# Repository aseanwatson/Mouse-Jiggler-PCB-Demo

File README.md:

# Mouse-Jiggler-PCB-Demo
This is a PCB designed in KiCAD as a demo for Seattle Makers.

It's based on [Arduino based Mouse Jiggler](https://github.com/MAKERSUN99/MAUS) 
published on GitHub. MAKERSUN99 published the schematic and the PCB as
a PDF so the circut and basic layout is clear, but not the original KiCAD
files.

It is a good demo because it can be incrementally designed. At its core,
it is a USB A male connector and an ATTINY85. The ATTINY can do raw GPIO
manipulation to handle USB connectivity and so it can emulate a mouse.

But USB devices should have ESD protection and so you can add that as a
pair of zener diodes and a capacitor.

Similarly, the ATTINY is supposed to have a capacitor close to VCC to condition
power for it.

Once that is done, you still ought to have a way to program the ATTINY so, you
can add a 1x5 pin header to connect to VCC, GND, PB2, PB3,and PB4.

After that, it's nice to have a LED and an associated resistor to show
activity.

Finally, you can add a WS2812B/NeoPixel for more interesting light effects.

## Steps to build it in KiCAD
Components:

|Part Description|Manufacturer Part Number|LCSC Part Number|
|-|-|-:|
|100nF Capacitor|CL21B104KBCNNNC|[C1711](https://www.lcsc.com/datasheet/lcsc_datasheet_2304140030_Samsung-Electro-Mechanics-CL21B104KBCNNNC_C1711.pdf)|
|100uF Capacitor|CL31A107MQHNNNE|[C15008](https://www.lcsc.com/datasheet/lcsc_datasheet_2304140030_Samsung-Electro-Mechanics-CL31A107MQHNNNE_C15008.pdf)|
|Zener Diode|MM1Z5226B|[C118713](https://www.lcsc.com/datasheet/lcsc_datasheet_2304140030_ST-Semtech-MM1Z5226B_C118713.pdf)|
|LED|XL-2012VRC|[C7371913](https://www.lcsc.com/datasheet/lcsc_datasheet_2402181500_XINGLIGHT-XL-2012VRC_C7371913.pdf)|
|1x5 male header|DS1021-1x5SF11-B|[C7430361](https://www.lcsc.com/datasheet/lcsc_datasheet_2312201431_CONNFLY-Elec-DS1021-1x5SF11-B_C7430361.pdf)|
|NeoPixel|WS2812B-B/T|[C2761795](https://www.lcsc.com/datasheet/lcsc_datasheet_2106062036_Worldsemi-WS2812B-B-T_C2761795.pdf)|
|68 Ohm Resistor|FRC0805J680 TS|[C2907341](https://www.lcsc.com/datasheet/lcsc_datasheet_2308241947_FOJAN-FRC0805J680-TS_C2907341.pdf)|
|1.5k Ohm Resistor|FRC0805J152 TS|[C2907290](https://www.lcsc.com/datasheet/lcsc_datasheet_2308241947_FOJAN-FRC0805J152-TS_C2907290.pdf)|
|220 Ohm Resistor|FRC0805J221 TS|[C2933537](https://www.lcsc.com/datasheet/lcsc_datasheet_2308241113_FOJAN-FRC0805J221-TS_C2933537.pdf)|
|10k Ohm Resistor|FRC0805J103TS|[C2930231](https://www.lcsc.com/datasheet/lcsc_datasheet_2308241947_FOJAN-FRC0805J103TS_C2930231.pdf)|
|ATTiny85 MPU|ATTINY85-20SU|[C89852](https://www.lcsc.com/datasheet/lcsc_datasheet_2011170235_Microchip-Tech-ATTINY85-20SU_C89852.pdf)|
|Male USB A Connector|KH-USB180-AM-4P|[C2828094](https://www.lcsc.com/datasheet/lcsc_datasheet_2105241835_Shenzhen-Kinghelm-Elec-KH-USB180-AM-4P_C2828094.pdf)|

KiCAD has the footprints and symbols for most of the above, but you need
to get the footprints from LCSC for three. To do that run this PowerShell:

``` powershell
cd $env:TEMP
python -m venv easyeda2kicad\.venv
. .\easyeda2kicad\.venv\Scripts\Activate.ps1
easyeda2kicad.exe --full --lcsc_id=C2761795
easyeda2kicad.exe --full --lcsc_id=C89852
easyeda2kicad.exe --full --lcsc_id=C2828094
```

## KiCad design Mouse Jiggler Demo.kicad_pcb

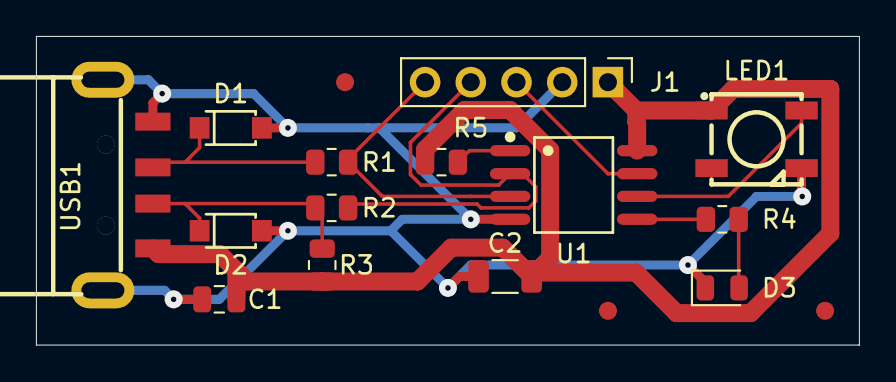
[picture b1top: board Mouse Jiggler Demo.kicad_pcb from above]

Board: 2 copper layers, 45.7 x 17.1 mm, 14 parts (0 on the bottom side), 11 nets.

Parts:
C1: 100n; C_0805_2012Metric
C2: 100u; C_1206_3216Metric
D1, D2: BZT52-C3V3_R1_00001; SOD-123_L2.7-W1.6-LS3.8-RD
D3: LED; LED_0805_2012Metric
J1: Conn_01x05_Pin; PinHeader_1x05_P2.54mm_Vertical
LED1: WS2812B-XF02/W; LED-SMD_4P-L5.0-W5.0-TL
R1, R2: 68; R_0805_2012Metric
R3: 1k5; R_0805_2012Metric
R4: 220; R_0805_2012Metric
R5: 10k; R_0805_2012Metric
U1: ATTINY85-20SUR; SOIC-8_L5.3-W5.3-P1.27-LS8.0-BL
USB1: U-G-04WS-W-04; USB-TH_U-G-04WS-W-04

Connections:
+5V: C1.1, C2.2, J1.1, LED1.1 (VDD), R3.1, R5.1, U1.8 (VCC), USB1.1 (VCC)
D+ PB4: J1.5, R1.2, U1.3 (PB4)
D- PB3: J1.4, R2.2, U1.2 (PB3)
GND: C1.2, C2.1, D1.2 (A), D2.2 (A), D3.1 (K), J1.2, LED1.3 (VSS), U1.4 (GND), USB1.4 (GND), USB1.5, USB1.6
LED: R4.1, U1.5 (PB0)
unnamed: D1.1 (C), R1.1, USB1.3 (D+)
unnamed: D2.1 (C), R2.1, R3.2, USB1.2 (D-)
unnamed: D3.2 (A), R4.2
unnamed: R5.2, U1.1 (PB5)
PB2: J1.3, U1.7 (PB2)
RGB: LED1.4 (DIN), U1.6 (PB1)

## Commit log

2024-07-10 PCB as ordered from JLCPCB
2024-07-10 Description of project in README.md
2024-07-16 Make overview markdown
2024-07-16 Make first flowchart simpler.
